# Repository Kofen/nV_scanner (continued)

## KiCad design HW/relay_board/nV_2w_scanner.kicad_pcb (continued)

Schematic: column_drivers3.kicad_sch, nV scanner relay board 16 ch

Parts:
C8, C9: 10uF; C_0603_1608Metric
C18: 100uF 6.3v; CP_EIA-7343-31_Kemet-D
Q8, Q9: FMB2227A; SuperSOT-6
R15, R16, R17, R18: 3.3k; R_0603_1608Metric

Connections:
+5V: C8.1, C9.1, C18.1, Q8.2 (E2), Q9.2 (E2); also elsewhere on the board
/Col_7: R15.1, R16.1; also elsewhere on the board
/Col_8: R17.1, R18.1; also elsewhere on the board
/Input_relays_13_16/rs4a3: Q8.4 (C2), Q8.6 (C1); also elsewhere on the board
/Input_relays_13_16/rs4b3: Q9.4 (C2), Q9.6 (C1); also elsewhere on the board
GND: C8.2, C9.2, C18.2, Q8.5 (E1), Q9.5 (E1); also elsewhere on the board
unnamed: Q8.1 (B1), R16.2
unnamed: Q8.3 (B2), R15.2
unnamed: Q9.1 (B1), R18.2
unnamed: Q9.3 (B2), R17.2

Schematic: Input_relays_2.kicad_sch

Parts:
D42, D46, D50, D54, D61, D62, D63, D64: APHBM2012L; LED_Kingbright_APHBM2012_2x1.25mm
J31, J35, J39, J43: Conn_01x02; PinHeader_1x02_P2.54mm_Vertical
J32, J36, J40, J44: Shield; SolderWirePad_1x01_SMD_3x5mm
J33, J37, J41, J45: +; SolderWirePad_1x01_SMD_3x5mm
J34, J38, J42, J46: -; SolderWirePad_1x01_SMD_3x5mm
K9, K10, K11, K12, K13, K14, K15, K16: TX2SA-L-3V-1; Relay_DPDT_Omron_G6S-2F
R26, R30, R34, R38, R45, R46, R47, R48: 330R; R_0603_1608Metric

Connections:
/A+: K9.4, K11.4, K13.4, K15.4; also elsewhere on the board
/A-: K9.9, K11.9, K13.9, K15.9; also elsewhere on the board
/B+: K10.4, K12.4, K14.4, K16.4; also elsewhere on the board
/B-: K10.9, K12.9, K14.9, K16.9; also elsewhere on the board
/Input_relays_5_8/ch1+: J33.1, K9.5, K10.5
/Input_relays_5_8/ch1-: J34.1, K9.8, K10.8
/Input_relays_5_8/ch2+: J37.1, K11.5, K12.5
/Input_relays_5_8/ch2-: J38.1, K11.8, K12.8
/Input_relays_5_8/ch3+: J41.1, K13.5, K14.5
/Input_relays_5_8/ch3-: J42.1, K13.8, K14.8
/Input_relays_5_8/ch4+: J45.1, K15.5, K16.5
/Input_relays_5_8/ch4-: J46.1, K15.8, K16.8
/Input_relays_5_8/rr1a1: D42.1 (A1), D42.3 (A2), K9.12; also elsewhere on the board
/Input_relays_5_8/rr1b1: D61.1 (A1), D61.3 (A2), K10.12; also elsewhere on the board
/Input_relays_5_8/rr2a1: D46.1 (A1), D46.3 (A2), K11.12; also elsewhere on the board
/Input_relays_5_8/rr2b1: D62.1 (A1), D62.3 (A2), K12.12; also elsewhere on the board
/Input_relays_5_8/rr3a1: D50.1 (A1), D50.3 (A2), K13.12; also elsewhere on the board
/Input_relays_5_8/rr3b1: D63.1 (A1), D63.3 (A2), K14.12; also elsewhere on the board
/Input_relays_5_8/rr4a1: D54.1 (A1), D54.3 (A2), K15.12; also elsewhere on the board
/Input_relays_5_8/rr4b1: D64.1 (A1), D64.3 (A2), K16.12; also elsewhere on the board
/Input_relays_5_8/rs2b1: K10.1, K12.1, K14.1, K16.1, R45.2, R46.2, R47.2, R48.2; also elsewhere on the board
/Input_relays_5_8/rs3a1: K9.1, K11.1, K13.1, K15.1, R26.2, R30.2, R34.2, R38.2; also elsewhere on the board
GUARD: J31.1, J35.1, J39.1, J43.1; also elsewhere on the board
unnamed: D42.2 (K1), D42.4 (K2), R26.1
unnamed: D46.2 (K1), D46.4 (K2), R30.1
unnamed: D50.2 (K1), D50.4 (K2), R34.1
unnamed: D54.2 (K1), D54.4 (K2), R38.1
unnamed: D61.2 (K1), D61.4 (K2), R45.1
unnamed: D62.2 (K1), D62.4 (K2), R46.1
unnamed: D63.2 (K1), D63.4 (K2), R47.1
unnamed: D64.2 (K1), D64.4 (K2), R48.1
unnamed: J31.2, J32.1
unnamed: J35.2, J36.1
unnamed: J39.2, J40.1
unnamed: J43.2, J44.1

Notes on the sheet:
Pin header to connect shield to guard, normally open
Channels 1 - 4 (5 - 8, n to n), read left to right

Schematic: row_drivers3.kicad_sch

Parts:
C12: 10uF; C_0603_1608Metric
C22: 100uF 6.3v; CP_EIA-7343-31_Kemet-D
D31, D32: 1N4148W; D_SOD-123
D33, D34, D35, D36, D37, D38, D39, D40: BAV99; SOT-23
Q12: FMB2227A; SuperSOT-6
R23, R24: 1k; R_0603_1608Metric

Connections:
+5V: C12.2, C22.1, D31.1 (K), Q12.2 (E2); also elsewhere on the board
/Input_relays_1_4/rr4a: D33.3 (K); also elsewhere on the board
/Input_relays_1_4/rr4b: D34.3 (K); also elsewhere on the board
/Input_relays_5_8/rr4a1: D35.3 (K); also elsewhere on the board
/Input_relays_5_8/rr4b1: D36.3 (K); also elsewhere on the board
/Input_relays_9_12/rr4a2: D37.3 (K); also elsewhere on the board
/Input_relays_9_12/rr4b2: D38.3 (K); also elsewhere on the board
/Input_relays_13_16/rr4a3: D39.3 (K); also elsewhere on the board
/Input_relays_13_16/rr4b3: D40.3 (K); also elsewhere on the board
/Row_l_4: R24.1; also elsewhere on the board
/nRow_h_4: R23.1; also elsewhere on the board
GND: C12.1, C22.2, D32.2 (A), Q12.5 (E1); also elsewhere on the board
unnamed: D31.2 (A), D33.2 (A), D34.2 (A), D35.2 (A), D36.2 (A), D37.2 (A), D38.2 (A), D39.2 (A), D40.2 (A), Q12.6 (C1)
unnamed: D32.1 (K), D33.1 (K), D34.1 (K), D35.1 (K), D36.1 (K), D37.1 (K), D38.1 (K), D39.1 (K), D40.1 (K), Q12.4 (C2)
unnamed: Q12.1 (B1), R24.2
unnamed: Q12.3 (B2), R23.2

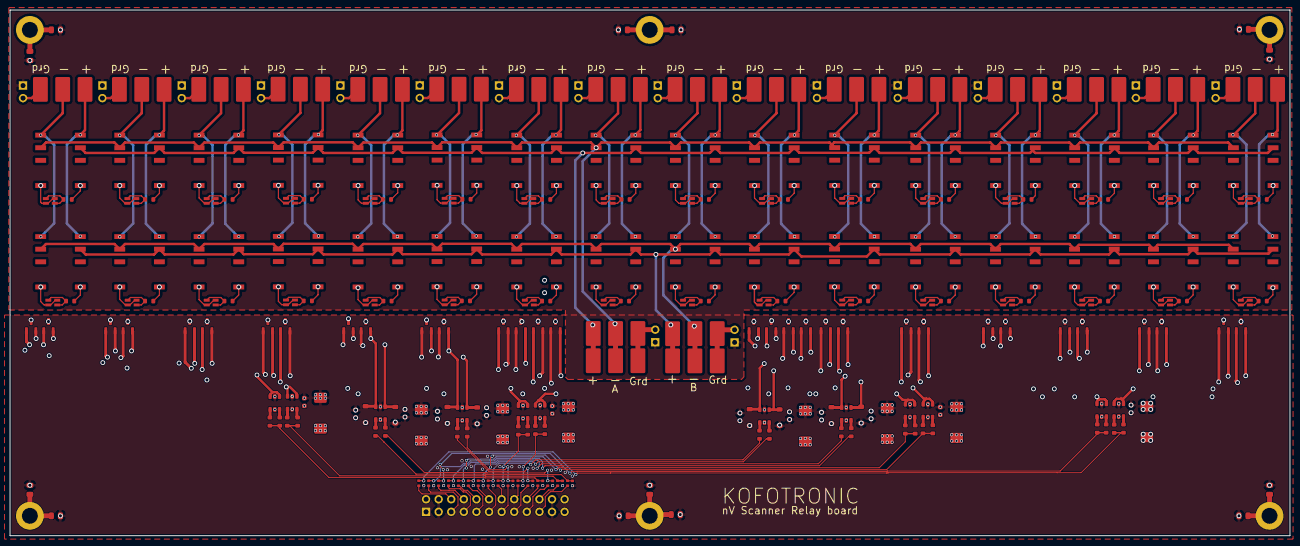
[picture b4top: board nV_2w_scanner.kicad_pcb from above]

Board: 6 copper layers, 258.1 x 106.0 mm, 322 parts (0 on the bottom side), 199 nets.

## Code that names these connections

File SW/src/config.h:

#pragma once

#define DEVICE_NAME "Ethernet2GPIB Gateway v1.1 (AR488 v0.53.03)\n"

#define LED_R 13
#define LED_G 35
#define LED_B 34


// This is needed, and debugPort should point to Serial if you want to use the serial menu
#define DEBUG_ENABLE
// define USE_SERIALMENU if you want a basic menu on the serial console for amongst others IP address setting.
#define USE_SERIALMENU

#define DISABLE_WEB_SERVER
// define USE_WEBSERVER if you want to use a very basic web page server that serves a static explanation page.
// It is not interactive, just a cherry on the cake with help text.
// This is mainly meant to be used with the VXI server, but it should work with the Prologix server as long as ROM permits (it will be very close if not over the limit).
#ifndef DISABLE_WEB_SERVER
#define USE_WEBSERVER
#endif

#ifndef INTERFACE_PROLOGIX
#define INTERFACE_VXI11
#endif
// and if you define both, well, you'll have to deal with the compiler telling you there is not enough ROM.


// for the Prologix server: 
#define AR_ETHERNET_PORT
#define PROLOGIX_PORT 1234

// For the VXI server:
#define VXI11_PORT 9010
// Maximum number of clients for the VXI server:
// Max MAX_SOCK_NUM sockets on the device. You will likely not even be able to reach that number, because of other sockets open or busy closing
#define MAX_VXI_CLIENTS MAX_SOCK_NUM
// set LOG_VXI_DETAILS to 0 or 1, depending on whether you want to see VXI details on the debugPort
// setting to 1 messes up the serial menu a bit
#define LOG_VXI_DETAILS 0

// set LOG_WEB_DETAILS to 0 or 1, depending on whether you want to see Web server details on the debugPort
// setting to 1 messes up the serial menu a bit
#define LOG_WEB_DETAILS 0

// if you activate this, the serial menu will be messier. 
// Only activate this when you want to see memory usage 
// and other details in auto refresh on the console.
// #define LOG_STATS_ON_CONSOLE

// EEPROM use: 
// Writing the 24AA256 is somehow broken, so we can also write via the GPIB configuration
#define AR488_GPIBconf_EXTEND
